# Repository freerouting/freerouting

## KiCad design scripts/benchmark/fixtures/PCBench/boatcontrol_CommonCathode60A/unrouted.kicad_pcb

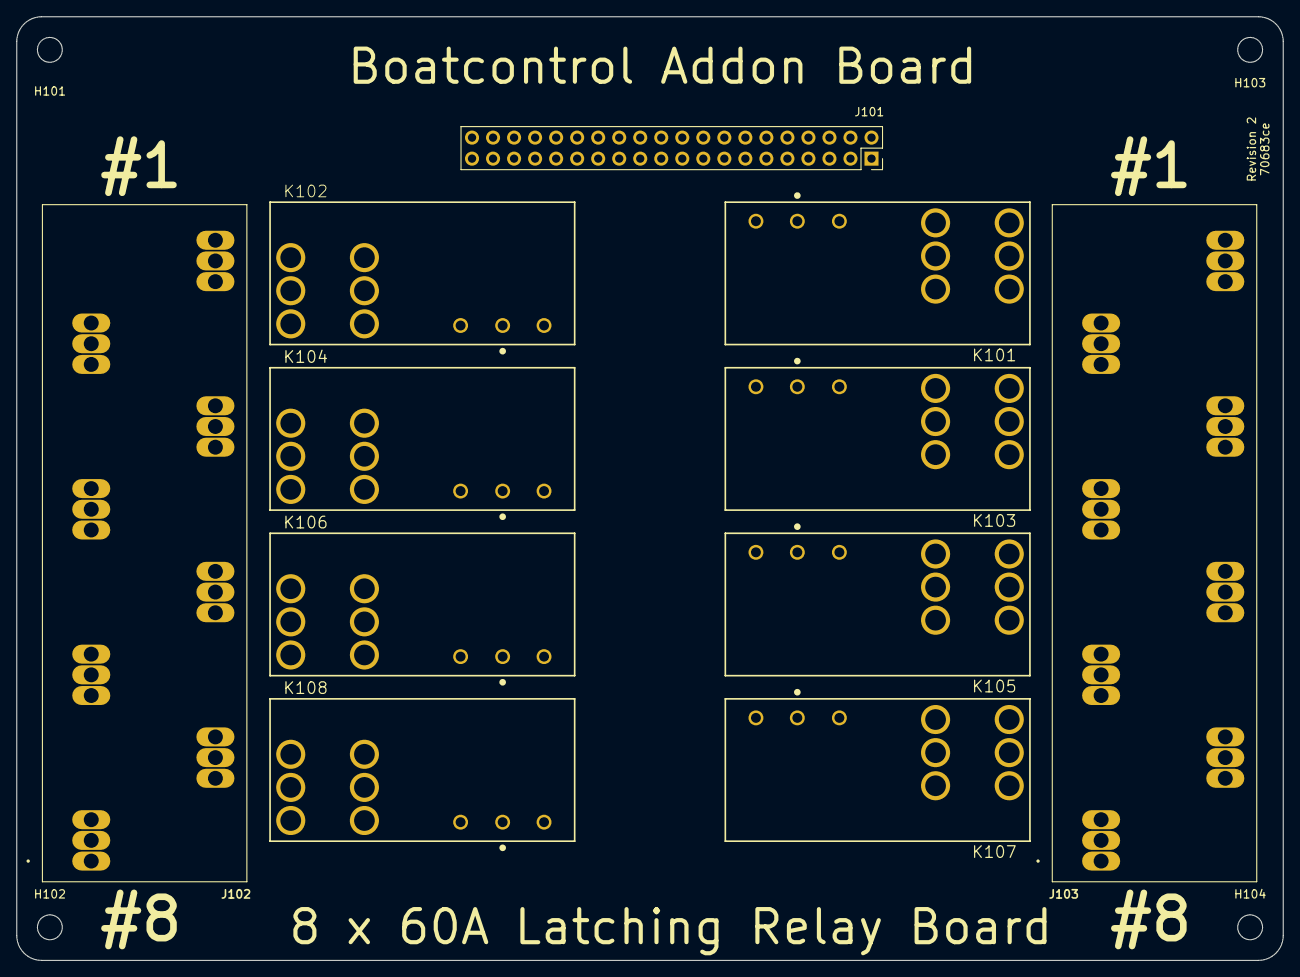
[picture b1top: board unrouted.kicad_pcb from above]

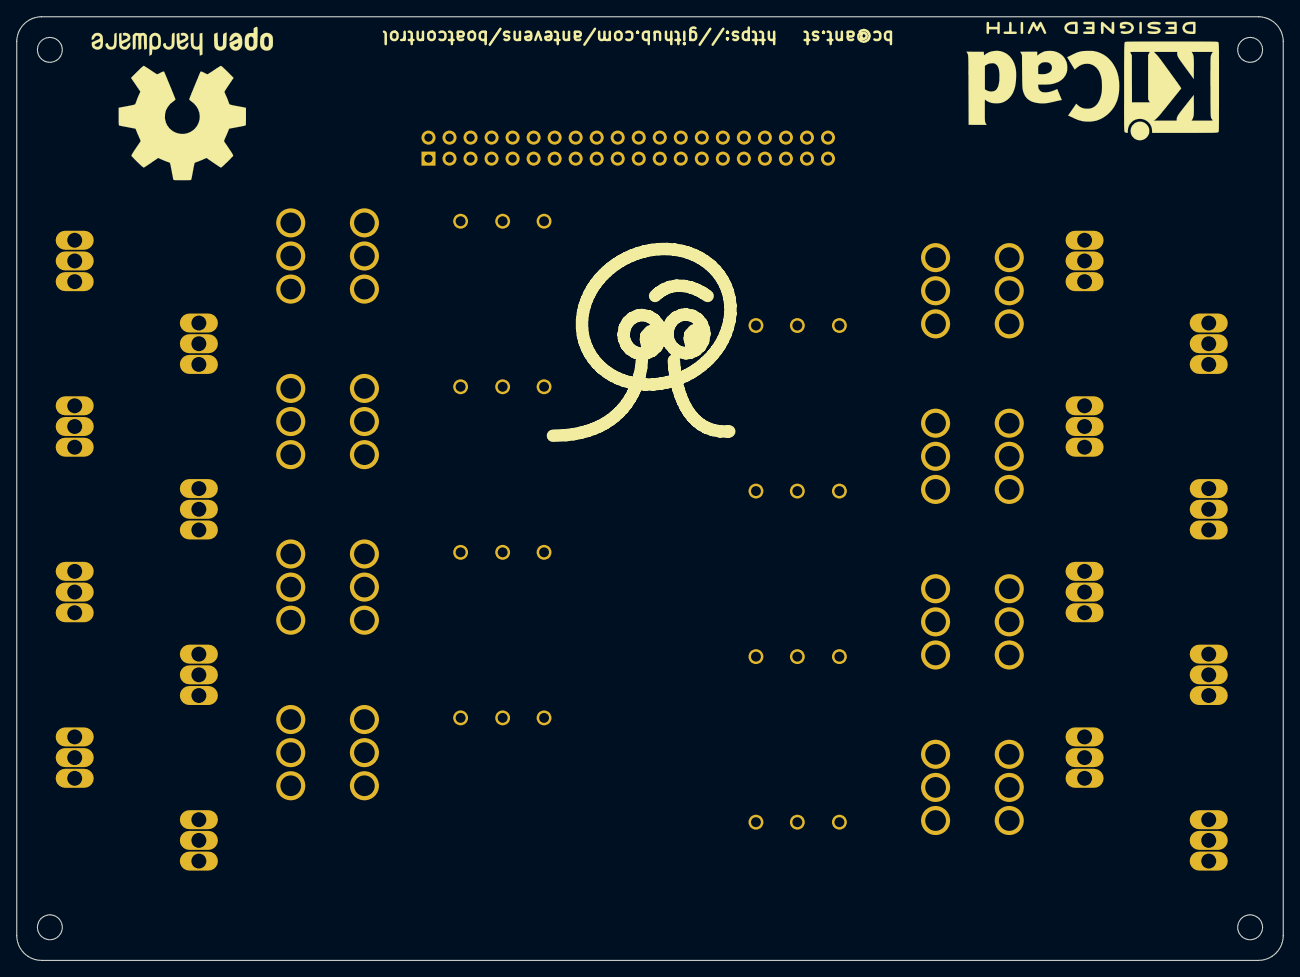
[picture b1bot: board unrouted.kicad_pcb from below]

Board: 4 copper layers, 153.0 x 114.0 mm, 18 parts (3 on the bottom side), 33 nets, no tracks yet.

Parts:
G102: LOGO_ANT; Ant_Logo_SilkScreen
H101, H102, H103, H104: MountingHole; MountingHole_3mm
J101: Conn_02x20_Odd_Even Header; PinSocket_2x20_P2.54mm_Vertical
J102, J103: TBL008V-1000-08BE; CUI_TBL008V-1000-08BE
K101, K102, K103, K104, K105, K106, K107, K108: EW60-1A3-CL12D04; TE_2071366-2
LOGO101: Logo_Open_Hardware_Large; KiCad-Logo2_12mm_SilkScreen
LOGO102: Logo_Open_Hardware_Large; OSHW-Logo2_24.3x20mm_SilkScreen

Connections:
/K1_COIL_OFF: J101.3, J101.4, K101.A2
/K1_COIL_ON: J101.1, J101.2, K101.A3
/K1_IN: J102.81, J102.82, J102.83, K101.4, K101.5, K101.6
/K1_OUT: J103.81, J103.82, J103.83, K101.1, K101.2, K101.3
/K2_COIL_OFF: J101.7, J101.8, K102.A3
/K2_COIL_ON: J101.5, J101.6, K102.A2
/K2_IN: J102.71, J102.72, J102.73, K102.1, K102.2, K102.3
/K2_OUT: J103.71, J103.72, J103.73, K102.4, K102.5, K102.6
/K3_COIL_OFF: J101.11, J101.12, K103.A2
/K3_COIL_ON: J101.9, J101.10, K103.A3
/K3_IN: J102.61, J102.62, J102.63, K103.4, K103.5, K103.6
/K3_OUT: J103.61, J103.62, J103.63, K103.1, K103.2, K103.3
/K4_COIL_OFF: J101.15, J101.16, K104.A3
/K4_COIL_ON: J101.13, J101.14, K104.A2
/K4_IN: J102.51, J102.52, J102.53, K104.1, K104.2, K104.3
/K4_OUT: J103.51, J103.52, J103.53, K104.4, K104.5, K104.6
/K5_COIL_OFF: J101.19, J101.20, K105.A2
/K5_COIL_ON: J101.17, J101.18, K105.A3
/K5_IN: J102.41, J102.42, J102.43, K105.4, K105.5, K105.6
/K5_OUT: J103.41, J103.42, J103.43, K105.1, K105.2, K105.3
/K6_COIL_OFF: J101.23, J101.24, K106.A3
/K6_COIL_ON: J101.21, J101.22, K106.A2
/K6_IN: J102.31, J102.32, J102.33, K106.1, K106.2, K106.3
/K6_OUT: J103.31, J103.32, J103.33, K106.4, K106.5, K106.6
/K7_COIL_OFF: J101.27, J101.28, K107.A2
/K7_COIL_ON: J101.25, J101.26, K107.A3
/K7_IN: J102.21, J102.22, J102.23, K107.4, K107.5, K107.6
/K7_OUT: J103.21, J103.22, J103.23, K107.1, K107.2, K107.3
/K8_COIL_OFF: J101.31, J101.32, K108.A3
/K8_COIL_ON: J101.29, J101.30, K108.A2
/K8_IN: J102.11, J102.12, J102.13, K108.1, K108.2, K108.3
/K8_OUT: J103.11, J103.12, J103.13, K108.4, K108.5, K108.6
GND: J101.33, J101.34, J101.35, J101.36, J101.37, J101.38, J101.39, J101.40, K101.A1, K102.A1, K103.A1, K104.A1, K105.A1, K106.A1, K107.A1, K108.A1

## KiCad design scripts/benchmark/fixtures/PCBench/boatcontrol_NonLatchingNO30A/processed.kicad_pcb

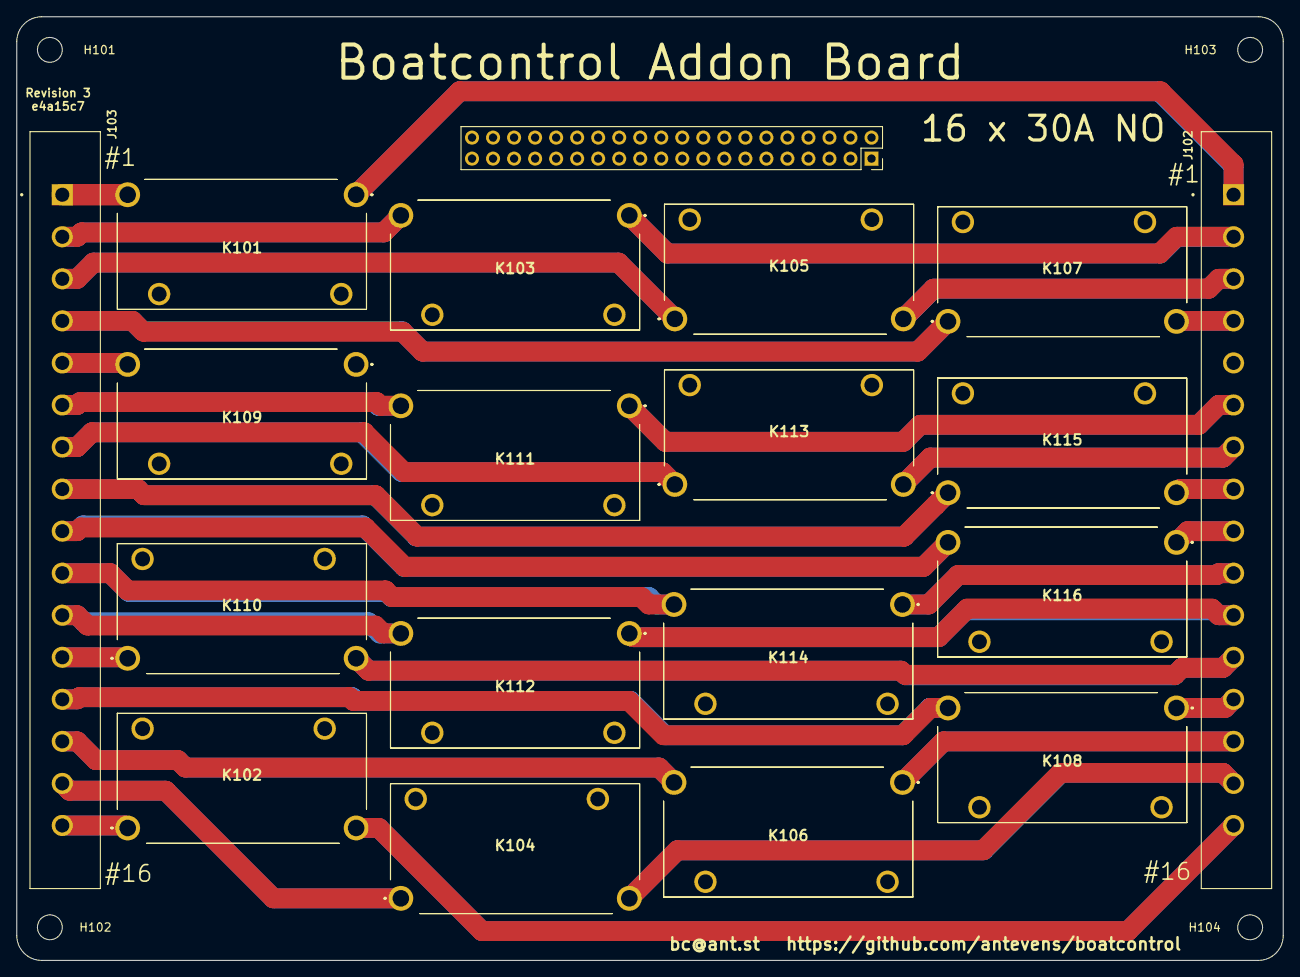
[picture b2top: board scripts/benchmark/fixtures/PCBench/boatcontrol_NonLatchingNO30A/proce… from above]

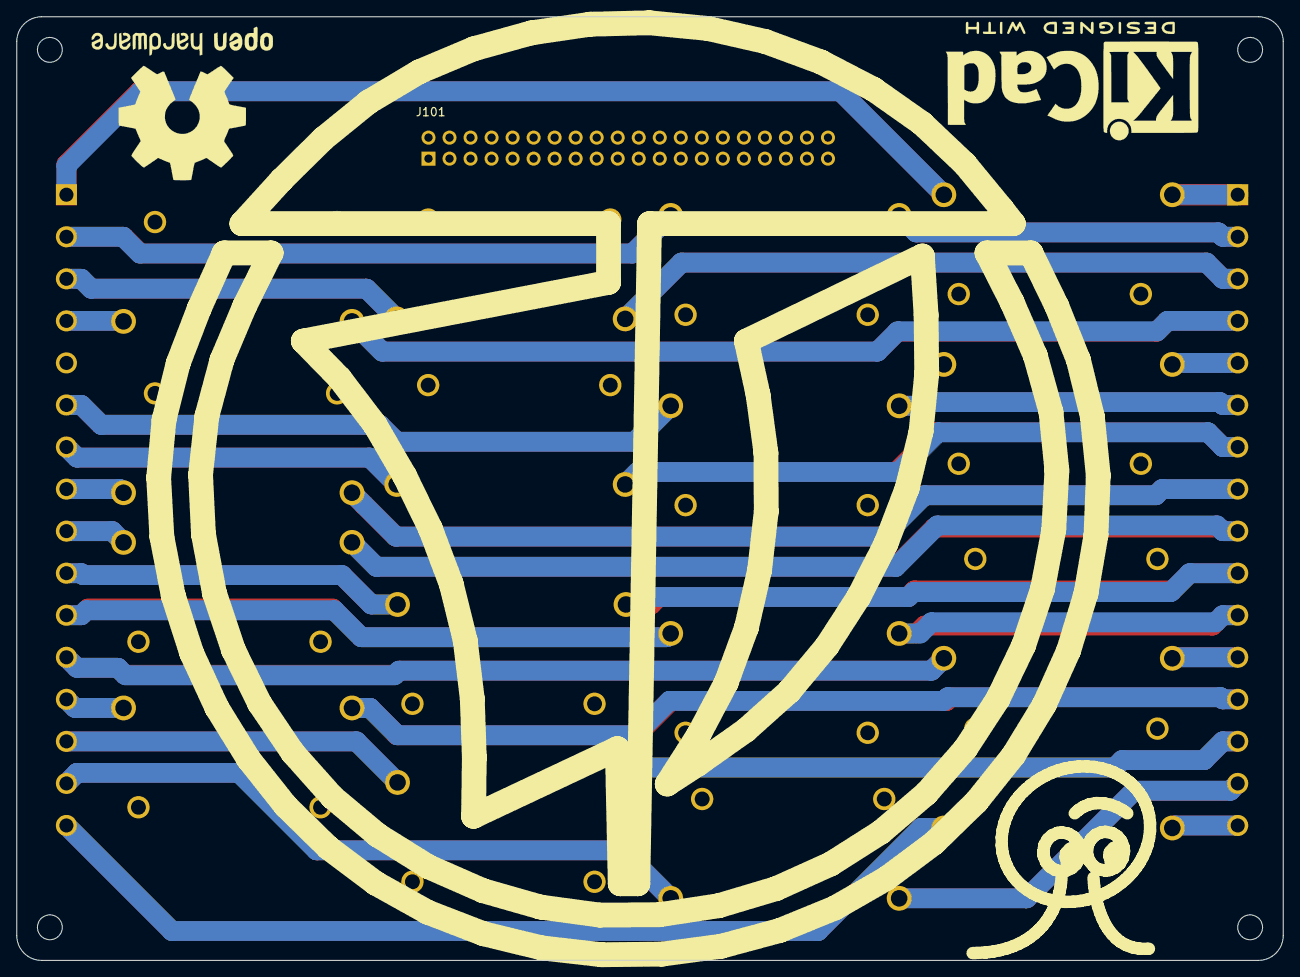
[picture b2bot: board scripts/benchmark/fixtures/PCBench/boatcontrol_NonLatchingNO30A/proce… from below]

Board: 4 copper layers, 153.0 x 114.0 mm, 27 parts (4 on the bottom side), 48 nets.

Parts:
G101: LOGO_RUGLUDALLUR; Rugludallur-Logo_SilkScreen
G102: LOGO_ANT; Ant_Logo_SilkScreen
H101, H102, H103, H104: MountingHole; MountingHole_3mm
J101: Conn_02x20_Odd_Even Header; PinSocket_2x20_P2.54mm_Vertical
J102, J103: TBP01R2W-508-16BE; CUI_TBP01R2W-508-16BE
K101, K102, K103, K104, K105, K106, K107, K108, K109, K110, K111, K112, K113, K114, K115, K116: ALFG2PF121
LOGO101: Logo_Open_Hardware_Large; KiCad-Logo2_12mm_SilkScreen
LOGO102: Logo_Open_Hardware_Large; OSHW-Logo2_24.3x20mm_SilkScreen

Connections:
/K1_COIL_ON: J101.1, J101.2, K101.4
/K2_COIL_ON: J101.3, J101.4, K103.4
/K3_COIL_ON: J101.5, J101.6, K105.3
/K4_COIL_ON: J101.7, J101.8, K107.3
/K5_COIL_ON: J101.9, J101.10, K109.4
/K6_COIL_ON: J101.11, J101.12, K111.4
/K7_COIL_ON: J101.13, J101.14, K113.3
/K8_COIL_ON: J101.15, J101.16, K115.3
/K9_COIL_ON: J101.17, J101.18, K116.4
/K10_COIL_ON: J101.19, J101.20, K114.4
/K11_COIL_ON: J101.21, J101.22, K112.4
/K12_COIL_ON: J101.23, J101.24, K110.3
/K13_COIL_ON: J101.25, J101.26, K108.4
/K14_COIL_ON: J101.27, J101.28, K106.4
/K15_COIL_ON: J101.29, J101.30, K104.3
/K16_COIL_ON: J101.31, J101.32, K102.3
GND: J101.33, J101.34, J101.35, J101.36, J101.37, J101.38, J101.39, J101.40, K101.3, K102.4, K103.3, K104.4, K105.4, K106.3, K107.4, K108.3, K109.3, K110.4, K111.3, K112.3, K113.4, K114.3, K115.4, K116.3
unnamed: J102.1, K101.1
unnamed: J102.2, K103.1
unnamed: J102.3, K105.2
unnamed: J102.4, K107.2
unnamed: J102.6, K111.1
unnamed: J102.7, K113.2
unnamed: J102.8, K115.2
unnamed: J102.9, K116.1
unnamed: J102.10, K114.1
unnamed: J102.11, K112.1
unnamed: J102.12, K110.2
unnamed: J102.13, K108.1
unnamed: J102.14, K106.1
unnamed: J102.15, K104.2
unnamed: J102.16, K102.2
unnamed: J103.1, K101.2
unnamed: J103.2, K103.2
unnamed: J103.3, K105.1
unnamed: J103.4, K107.1
unnamed: J103.5, K109.2
unnamed: J103.6, K111.2
unnamed: J103.7, K113.1
unnamed: J103.8, K115.1
unnamed: J103.9, K116.2
unnamed: J103.10, K114.2
unnamed: J103.11, K112.2
unnamed: J103.12, K110.1
unnamed: J103.13, K108.2
unnamed: J103.14, K106.2
unnamed: J103.15, K104.1
unnamed: J103.16, K102.1

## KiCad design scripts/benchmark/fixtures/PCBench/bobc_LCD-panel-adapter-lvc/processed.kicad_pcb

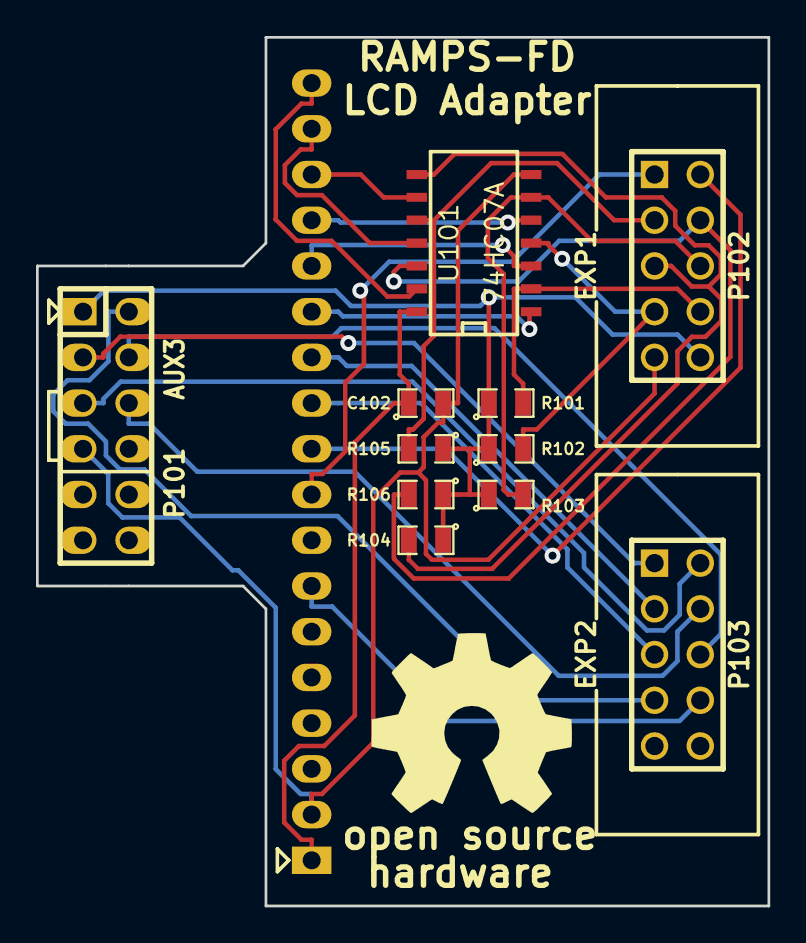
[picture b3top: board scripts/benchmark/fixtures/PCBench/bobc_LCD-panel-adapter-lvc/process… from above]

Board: 2 copper layers, 40.6 x 48.3 mm, 13 parts (1 on the bottom side), 25 nets.

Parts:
C102: 100nF; SM0805
J101: AUX4; pin_strip_18
M101: LOGO_OSHW; OSHW_logo_2
P101: AUX3; pin_strip_6x2
P102: EXP1; PIN_ARRAY_5x2_RMC
P103: EXP2; PIN_ARRAY_5x2_RMC
R101, R102, R103, R104, R105, R106: 10k; SM0805
U101: 74HC07A; SO14N

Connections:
+5V: P101.1, P102.10, R101.1, R102.1, R103.1, R104.1, R105.1, R106.1
/IOREF: C102.1, J101.1, U101.14
/LCD_D4_5V: P102.5, R104.2, U101.8
/LCD_D5_5V: P102.6, R103.2, U101.6
/LCD_D6_5V: P102.7, R102.2, U101.4
/LCD_D7_5V: P102.8, R101.2, U101.2
/LCD_E_5V: P102.3, R105.2, U101.10
/LCD_RS_5V: P102.4, R106.2, U101.12
BEEP: J101.9, P102.1
ENC1: J101.11, P103.5
ENC2: J101.12, P103.3
ENC_SW: J101.10, P102.2
GND: C102.2, J101.2, P101.7, P102.9, U101.7
LCD_D4: J101.16, U101.9
LCD_D5: J101.15, U101.5
LCD_D6: J101.14, U101.3
LCD_D7: J101.13, U101.1
LCD_E: J101.17, U101.11
LCD_RS: J101.18, U101.13
RESET: J101.7, P103.8
SD_CLK: P101.5, P103.2
SD_CS: P101.6, P103.4
SD_DETECT: P101.2, P103.7
SD_DI: P101.4, P103.6
SD_DO: P101.3, P103.1

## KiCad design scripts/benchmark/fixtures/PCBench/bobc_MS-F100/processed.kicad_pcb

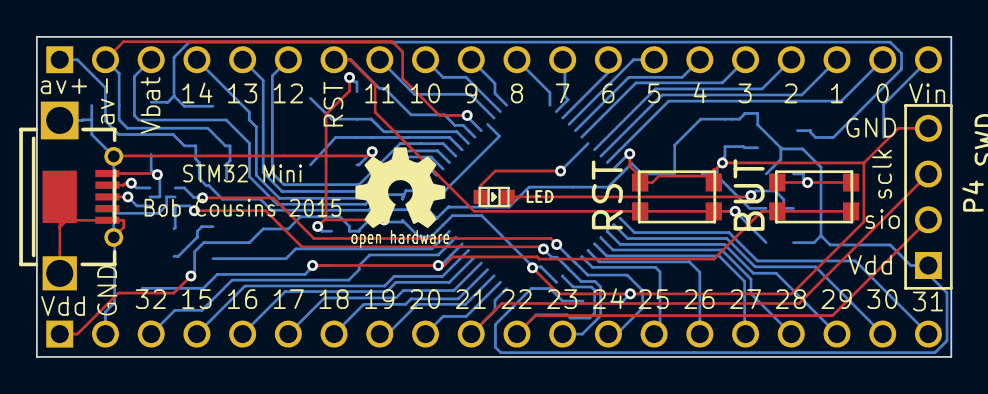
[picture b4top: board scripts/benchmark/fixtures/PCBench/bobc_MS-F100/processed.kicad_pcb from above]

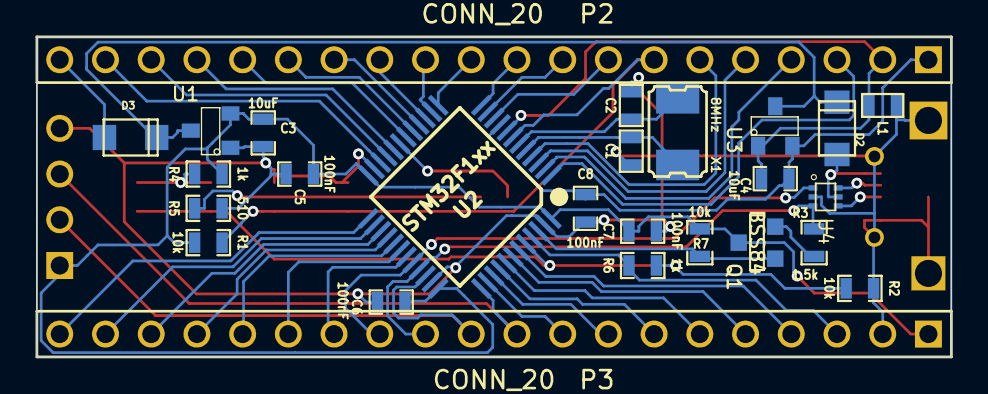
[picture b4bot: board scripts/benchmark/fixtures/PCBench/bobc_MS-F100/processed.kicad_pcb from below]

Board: 2 copper layers, 50.8 x 17.8 mm, 33 parts (26 on the bottom side), 52 nets.

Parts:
C1, C2: 20pF; SM0603_Capa
C3, C4: 10uF; SM0603_Capa
C5, C6, C7, C8: 100nF; SM0603_Capa
D1: LED; Led_0603
D2, D3: DIOD; do219ab
L1: IND; SM0603
M1: LOGO_OSHW; Logo_silk_OSHW_6x6mm
M2: PCB_GREEN_RMC; PCB_GREEN
P1: USBCONN; USB_MICRO_RMC
P2, P3: CONN_20; pin_header_2.54mm_1x20
P4: SWD; pin_header_2.54mm_1x4
Q1: BSS84; SOT23GDS
R1, R2, R7: 10k; SM0603_Resistor
R3: 1.5k; SM0603_Resistor
R4, R6: 1k; SM0603_Resistor
R5: 510; SM0603_Resistor
SW1: RST; SW_C&K_KMR4
SW2: BUT; SW_C&K_KMR4
U1, U3: MCP1703_SOT23; SOT23
U2: STM32F1xx; QFP48_0.5mm_7x7mm_SOT313_LPC1343
U4: NUF2042; SOT-563
X1: 8MHz; crystal_smd_5x3.2mm

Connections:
/AV+: C4.1, C8.1, P2.1, U2.9, U3.2
/AV-: C4.2, L1.2, P2.2, U2.8, U3.1
/BOOT0: R2.1, R6.2, SW2.1, U2.44
/D0: P2.19, U2.22
/D1: P2.18, U2.21
/D2: P2.17, U2.20
/D3: P2.16, U2.18
/D4: P2.15, U2.17
/D5: P2.14, U2.16
/D6: P2.13, U2.15
/D7: P2.12, U2.14
/D8: P2.11, U2.13
/D9: P2.10, U2.12
/D10: P2.9, U2.11
/D11: P2.8, U2.10
/D12: P2.6, U2.4
/D13: P2.5, U2.3
/D14: P2.4, U2.2
/D15: P3.4, U2.43
/D16: P3.5, U2.42
/D17: P3.6, U2.41
/D18: P3.7, U2.40
/D19: P3.8, U2.39
/D20: P3.9, U2.38
/D21_SWCLK: P3.10, P4.3, U2.37
/D22_SWIO: P3.11, P4.2, U2.34
/D23_USBDP: P3.12, R3.2, U2.33, U4.3
/D24_USBDM: P3.13, U2.32, U4.1
/D25: P3.14, U2.31
/D26: P3.15, U2.30
/D27: P3.16, U2.29
/D28: P3.17, U2.28
/D29: P3.18, U2.27
/D30: P3.19, U2.26
/D31: P3.20, U2.25
/D32: P3.3, R6.1, U2.45
/D33: D1.1, U2.19
/DISC: Q1.G, R7.2, U2.46
/VBAT: P2.3, U2.1
/VBUS: D2.1, P1.1, U4.5
/nRESET: P2.7, R1.2, SW1.2, U2.7
GND: C1.2, C2.2, C3.2, C5.2, C6.2, C7.2, C8.2, L1.1, P1.4, P1.5, P3.2, P4.4, R2.2, R5.2, SW1.1, U1.1, U2.23, U2.35, U2.47, U4.2
unnamed: R4.2, SW2.2
unnamed: D1.2, R5.1
unnamed: Q1.S, R3.1
unnamed: C1.1, U2.5, X1.1
unnamed: C2.1, U2.6, X1.2
unnamed: P1.3, U4.4
unnamed: D2.2, D3.2, U1.3, U3.3
unnamed: P1.2, U4.6
VDD: C3.1, C5.1, C6.1, C7.1, P3.1, P4.1, Q1.D, R1.1, R4.1, R7.1, U1.2, U2.24, U2.36, U2.48
VIN: D3.1, P2.20

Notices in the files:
scripts/benchmark/fixtures/PCBench/bobc_MS-F100/processed.kicad_pcb:
Copyright Under the Creative Commons Attribution License
